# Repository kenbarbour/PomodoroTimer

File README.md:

Pomodoro Timer
==============

This project provides the source files for building an arduino based timer to 
implement the Pomodoro time management method.

Project subdirectories
----------------------
 * **arduino/** - contains the source files for the arduino code
 * **hardware/** - contains the files to build the PCB and schematics

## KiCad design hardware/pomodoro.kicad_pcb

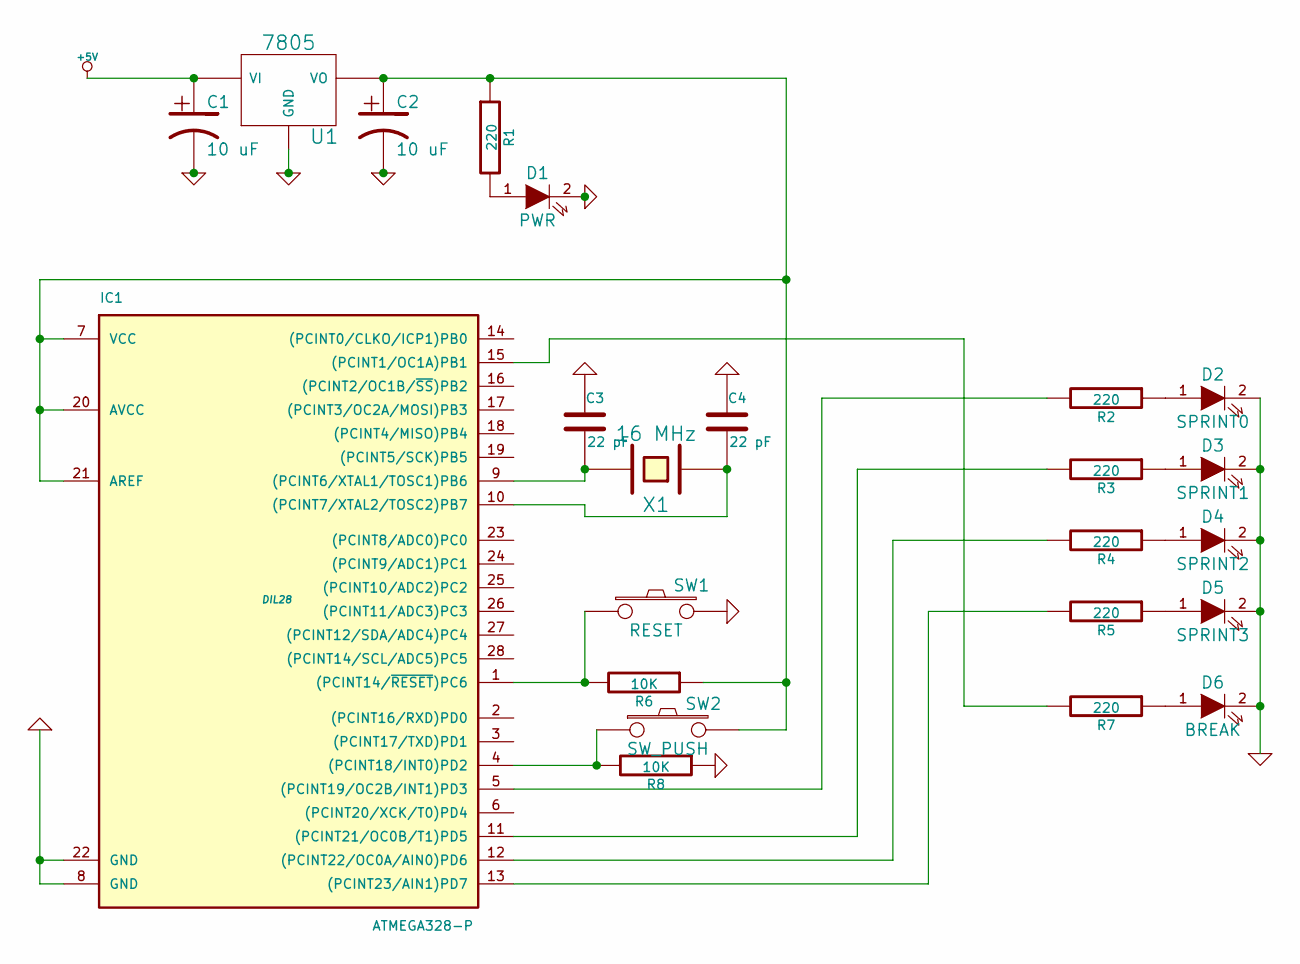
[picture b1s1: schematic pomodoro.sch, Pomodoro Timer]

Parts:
C1, C2: 10 uF
C3, C4: 22 pF
D1: PWR
D2: SPRINT0
D3: SPRINT1
D4: SPRINT2
D5: SPRINT3
D6: BREAK
IC1: ATMEGA328-P; DIL28
R1, R2, R3, R4, R5, R7: 220
R6, R8: 10K
SW1: RESET
SW2: SW_PUSH
U1: 7805
X1: 16 MHz

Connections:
+5V: C1.1, U1.VI
GND: C1.2, C2.2, C3.1, C4.1, D1.2 (K), D2.2 (K), D3.2 (K), D4.2 (K), D5.2 (K), D6.2 (K), IC1.8 (GND), IC1.22 (GND), R8.1, SW1.2, U1.GND
unnamed: C2.1, IC1.7 (VCC), IC1.20 (AVCC), IC1.21 (AREF), R1.1, R6.1, SW2.2, U1.VO
unnamed: C3.2, IC1.9 ((PCINT6/XTAL1/TOSC1)PB6), X1.2
unnamed: C4.2, IC1.10 ((PCINT7/XTAL2/TOSC2)PB7), X1.1
unnamed: D1.1 (A), R1.2
unnamed: D2.1 (A), R2.1
unnamed: D3.1 (A), R3.1
unnamed: D4.1 (A), R4.1
unnamed: D5.1 (A), R5.1
unnamed: D6.1 (A), R7.1
unnamed: IC1.1 ((PCINT14/~RESET~)PC6), R6.2, SW1.1
unnamed: IC1.4 ((PCINT18/INT0)PD2), R8.2, SW2.1
unnamed: IC1.5 ((PCINT19/OC2B/INT1)PD3), R2.2
unnamed: IC1.11 ((PCINT21/OC0B/T1)PD5), R3.2
unnamed: IC1.12 ((PCINT22/OC0A/AIN0)PD6), R4.2
unnamed: IC1.13 ((PCINT23/AIN1)PD7), R5.2
unnamed: IC1.15 ((PCINT1/OC1A)PB1), R7.2

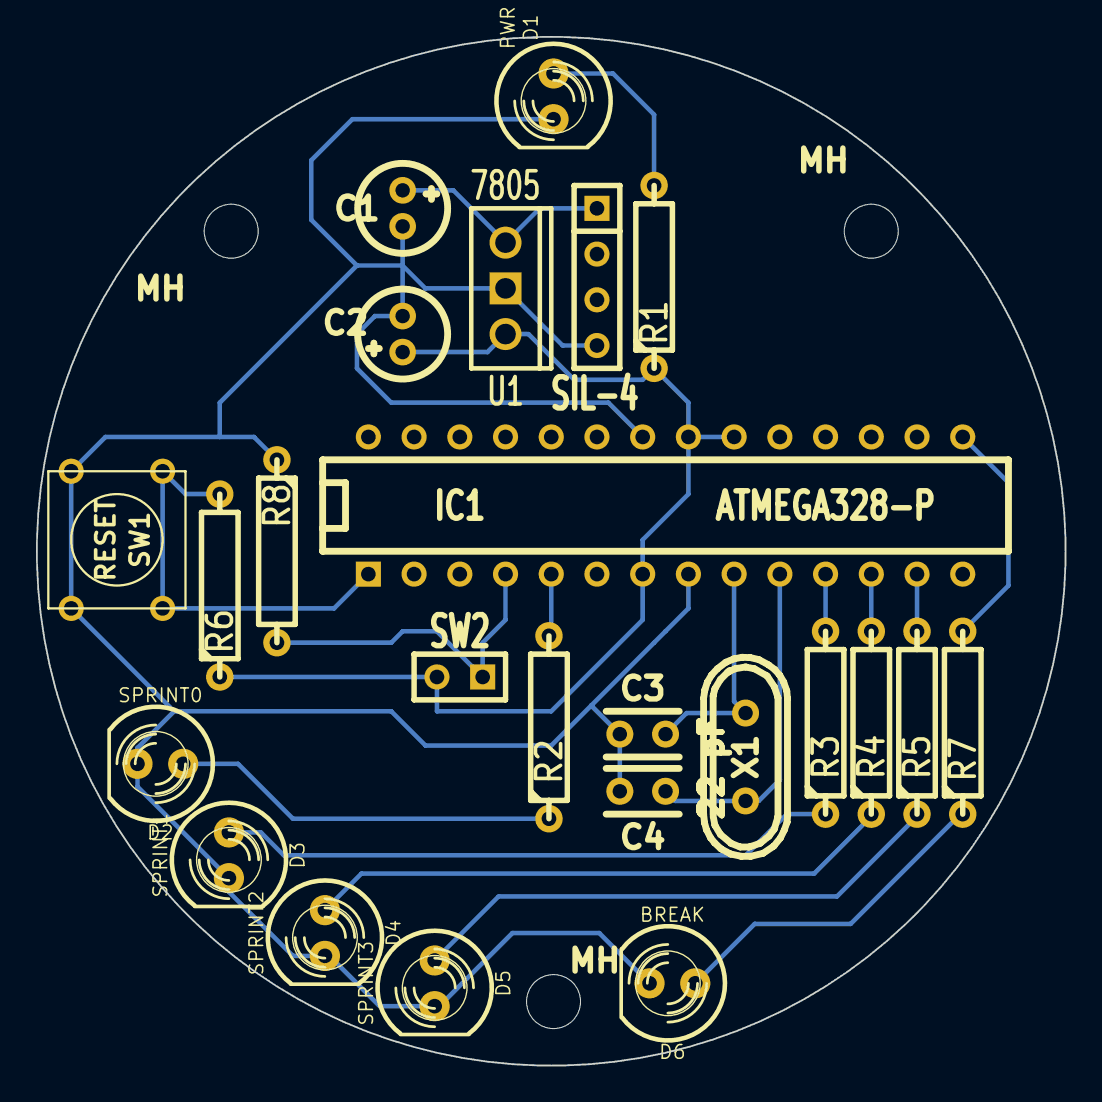
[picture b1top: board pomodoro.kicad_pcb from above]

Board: 2 copper layers, 57.1 x 57.2 mm, 27 parts (0 on the bottom side), 18 nets.

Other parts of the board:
MH: MountingHole_3mm_RevA_Date21Jun2010; MountingHole_3mm
MH#2, MH#3: MountingHole_3mm_RevA_Date21Jun2010; MountingHole_3mm
SIL-4: SIL-4

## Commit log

2016-03-10 started PCB layout; still need to check connections and footprints
2016-03-11 added a custom library
    need to fix the 7805 footprint
2016-03-11 Revert "added a custom library"
    This reverts commit 276737cbcb6067e06a546fe0e26b3fd12c06b826.
2016-03-11 finished working for the day, going home. still need to verify footprints before building pcb
2016-03-12 still wrestling with the schematic.
2016-03-14 Started pcb layout - routed power supply - routed 16mHz clock
2016-03-15 more layout of traces layout for PSU to ATMega reset and push button traced
    I may move D1, shift the PSU at AVR up, and make room for resistor layout for diodes
2016-03-15 need to reconfigure led output pins
2016-03-16 some knucklehead didnt retrace the LED he moved
2016-03-16 repinned the LEDs to prevent needing to use jumpers on PCB
2016-03-16 looks like everything is placed and connected on PCB. need to add mounting holes and a diagram for the parts to manufacture
2016-03-18 abstracting buttons in the arduino sketch arduino 1.0 wants files in a special directory
2016-03-19 Documented the Button class
2016-03-19 Restructed Button.h and .cpp - changed some function types to boolean - changed some data types to uint8_t - further separated interface from implementation
2016-03-19 program works the way it was intended, but... there are some poor practices being employed: - global variables - completely open implementation (need to separate interfaces) - timers need separate va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
2016-03-19 Added mounting holes to PCB and moved traces
2016-03-20 time constants should probably be unsigned long integers
2016-03-21 define DEBUG_POMODORO for debugging help - Calls Serial.print() in various function calls to help debugging - leaving this out significantly reduces compiled sketch size
2016-03-22 added dimensions to pcb drawing so I can start the case design
2016-03-24 fixed power led resistor value
2016-03-25 changed LED pins in code to match pins on PCB
2016-03-25 pcb first prototype is done. some things may need to be moved around
